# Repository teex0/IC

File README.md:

# IC 
Iniciação Científica da placa integrada do projeto RoboFEI-HT

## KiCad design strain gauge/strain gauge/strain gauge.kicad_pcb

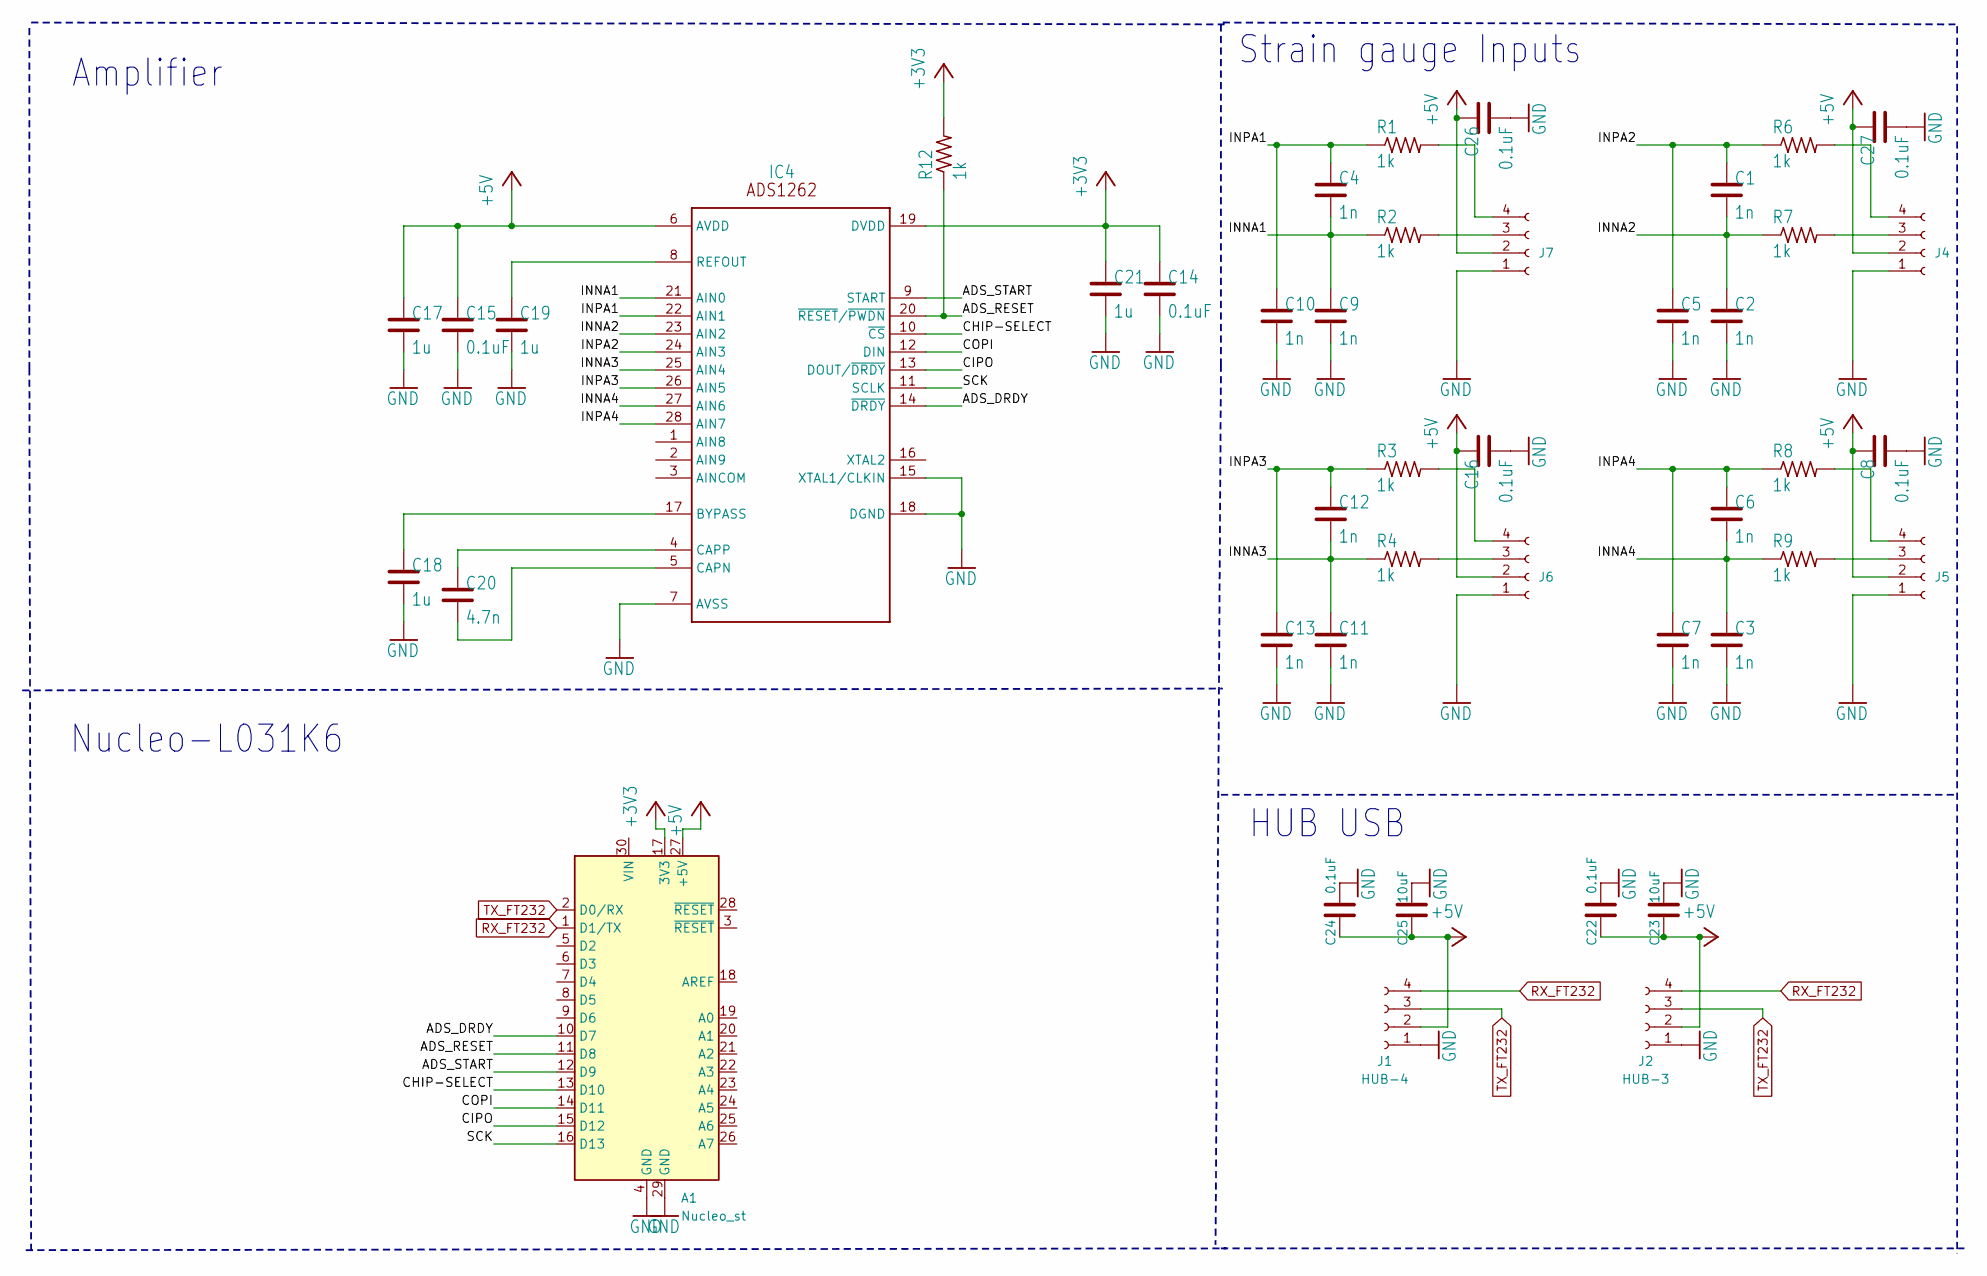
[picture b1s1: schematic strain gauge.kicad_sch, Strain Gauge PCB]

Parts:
A1: Nucleo_st; Arduino_Nano
C1, C2, C3, C4, C5, C6, C7, C9, C10, C11, C12, C13: 1n; C_1206_3216Metric_Pad1.33x1.80mm_HandSolder
C8, C14, C15, C16, C26, C27: 0.1uF; C_1206_3216Metric_Pad1.33x1.80mm_HandSolder
C17, C18, C19, C21: 1u; C_0201_0603Metric_Pad0.64x0.40mm_HandSolder
C20: 4.7n; C_1206_3216Metric_Pad1.33x1.80mm_HandSolder
C22, C24: 0.1uF; C_1206_3216Metric
C23, C25: 10uF; C_1206_3216Metric
IC4: ADS1262; ADS1262IPW
J1: HUB-4; PinHeader_1x04_P2.00mm_Vertical
J2: HUB-3; PinHeader_1x04_P2.00mm_Vertical
J4, J5, J6, J7: Conn_01x04_Socket; JST_PH_S4B-PH-K_1x04_P2.00mm_Horizontal
R1, R2, R3, R4, R6, R7, R8, R9, R12: 1k; R_1206_3216Metric_Pad1.30x1.75mm_HandSolder

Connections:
+3V3: A1.17 (3V3), C14.1, C21.1, IC4.19 (DVDD), R12.2
+5V: A1.27 (+5V), C8.1, C15.1, C16.1, C17.1, C22.1, C23.1, C24.1, C25.1, C26.1, C27.1, IC4.6 (AVDD), J1.2, J2.2, J4.2, J5.2, J6.2, J7.2
/ADS_DRDY: A1.10 (D7), IC4.14 (~DRDY)
/ADS_RESET: A1.11 (D8), IC4.20 (~RESET/~PWDN), R12.1
/ADS_START: A1.12 (D9), IC4.9 (START)
/CHIP-SELECT: A1.13 (D10), IC4.10 (~CS)
/CIPO: A1.15 (D12), IC4.13 (DOUT/~DRDY)
/COPI: A1.14 (D11), IC4.12 (DIN)
/INNA1: C4.2, C9.1, IC4.21 (AIN0), R2.1
/INNA2: C1.2, C2.1, IC4.23 (AIN2), R7.1
/INNA3: C11.1, C12.2, IC4.25 (AIN4), R4.1
/INNA4: C3.1, C6.2, IC4.27 (AIN6), R9.1
/INPA1: C4.1, C10.1, IC4.22 (AIN1), R1.1
/INPA2: C1.1, C5.1, IC4.24 (AIN3), R6.1
/INPA3: C12.1, C13.1, IC4.26 (AIN5), R3.1
/INPA4: C6.1, C7.1, IC4.28 (AIN7), R8.1
/SCK: A1.16 (D13), IC4.11 (SCLK)
GND: A1.4 (GND), A1.29 (GND), C2.2, C3.2, C5.2, C7.2, C8.2, C9.2, C10.2, C11.2, C13.2, C14.2, C15.2, C16.2, C17.2, C18.2, C19.2, C21.2, C22.2, C23.2, C24.2, C25.2, C26.2, C27.2, IC4.7 (AVSS), IC4.15 (XTAL1/CLKIN), IC4.18 (DGND), J1.1, J2.1, J4.1, J5.1, J6.1, J7.1
unnamed: C18.1, IC4.17 (BYPASS)
unnamed: C20.2, IC4.5 (CAPN)
unnamed: C20.1, IC4.4 (CAPP)
unnamed: C19.1, IC4.8 (REFOUT)
unnamed: J4.3, R7.2
unnamed: J4.4, R6.2
unnamed: J5.3, R9.2
unnamed: J5.4, R8.2
unnamed: J6.3, R4.2
unnamed: J6.4, R3.2
unnamed: J7.3, R2.2
unnamed: J7.4, R1.2
RX_FT232: A1.1 (D1/TX), J1.4, J2.4
TX_FT232: A1.2 (D0/RX), J1.3, J2.3

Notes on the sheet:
Strain gauge Inputs
Amplifier
Nucleo-L031K6
HUB USB

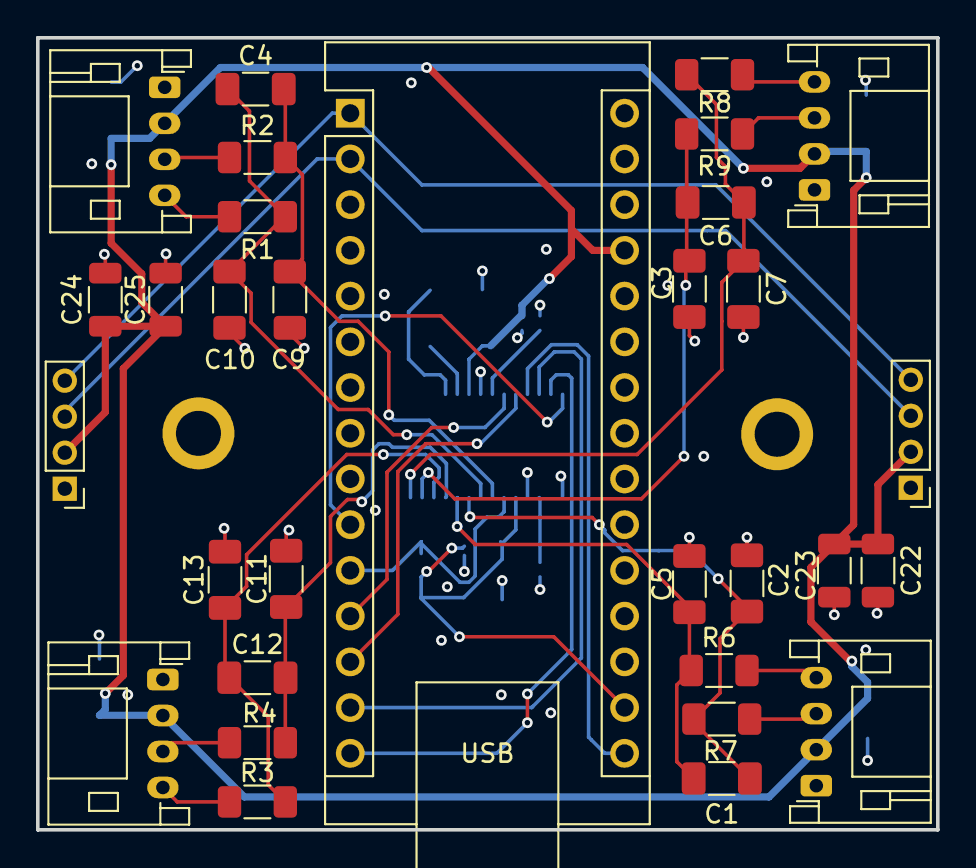
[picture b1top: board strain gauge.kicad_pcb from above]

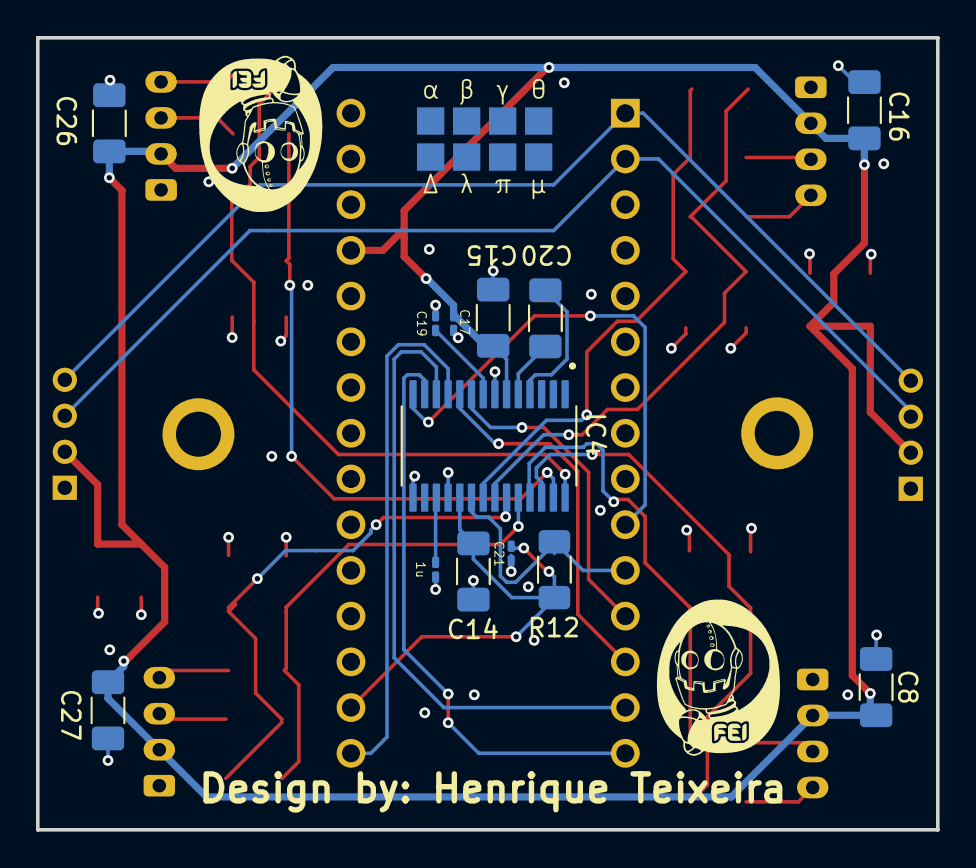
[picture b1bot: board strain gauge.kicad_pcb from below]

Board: 4 copper layers, 50.0 x 44.0 mm, 44 parts (13 on the bottom side), 32 nets.

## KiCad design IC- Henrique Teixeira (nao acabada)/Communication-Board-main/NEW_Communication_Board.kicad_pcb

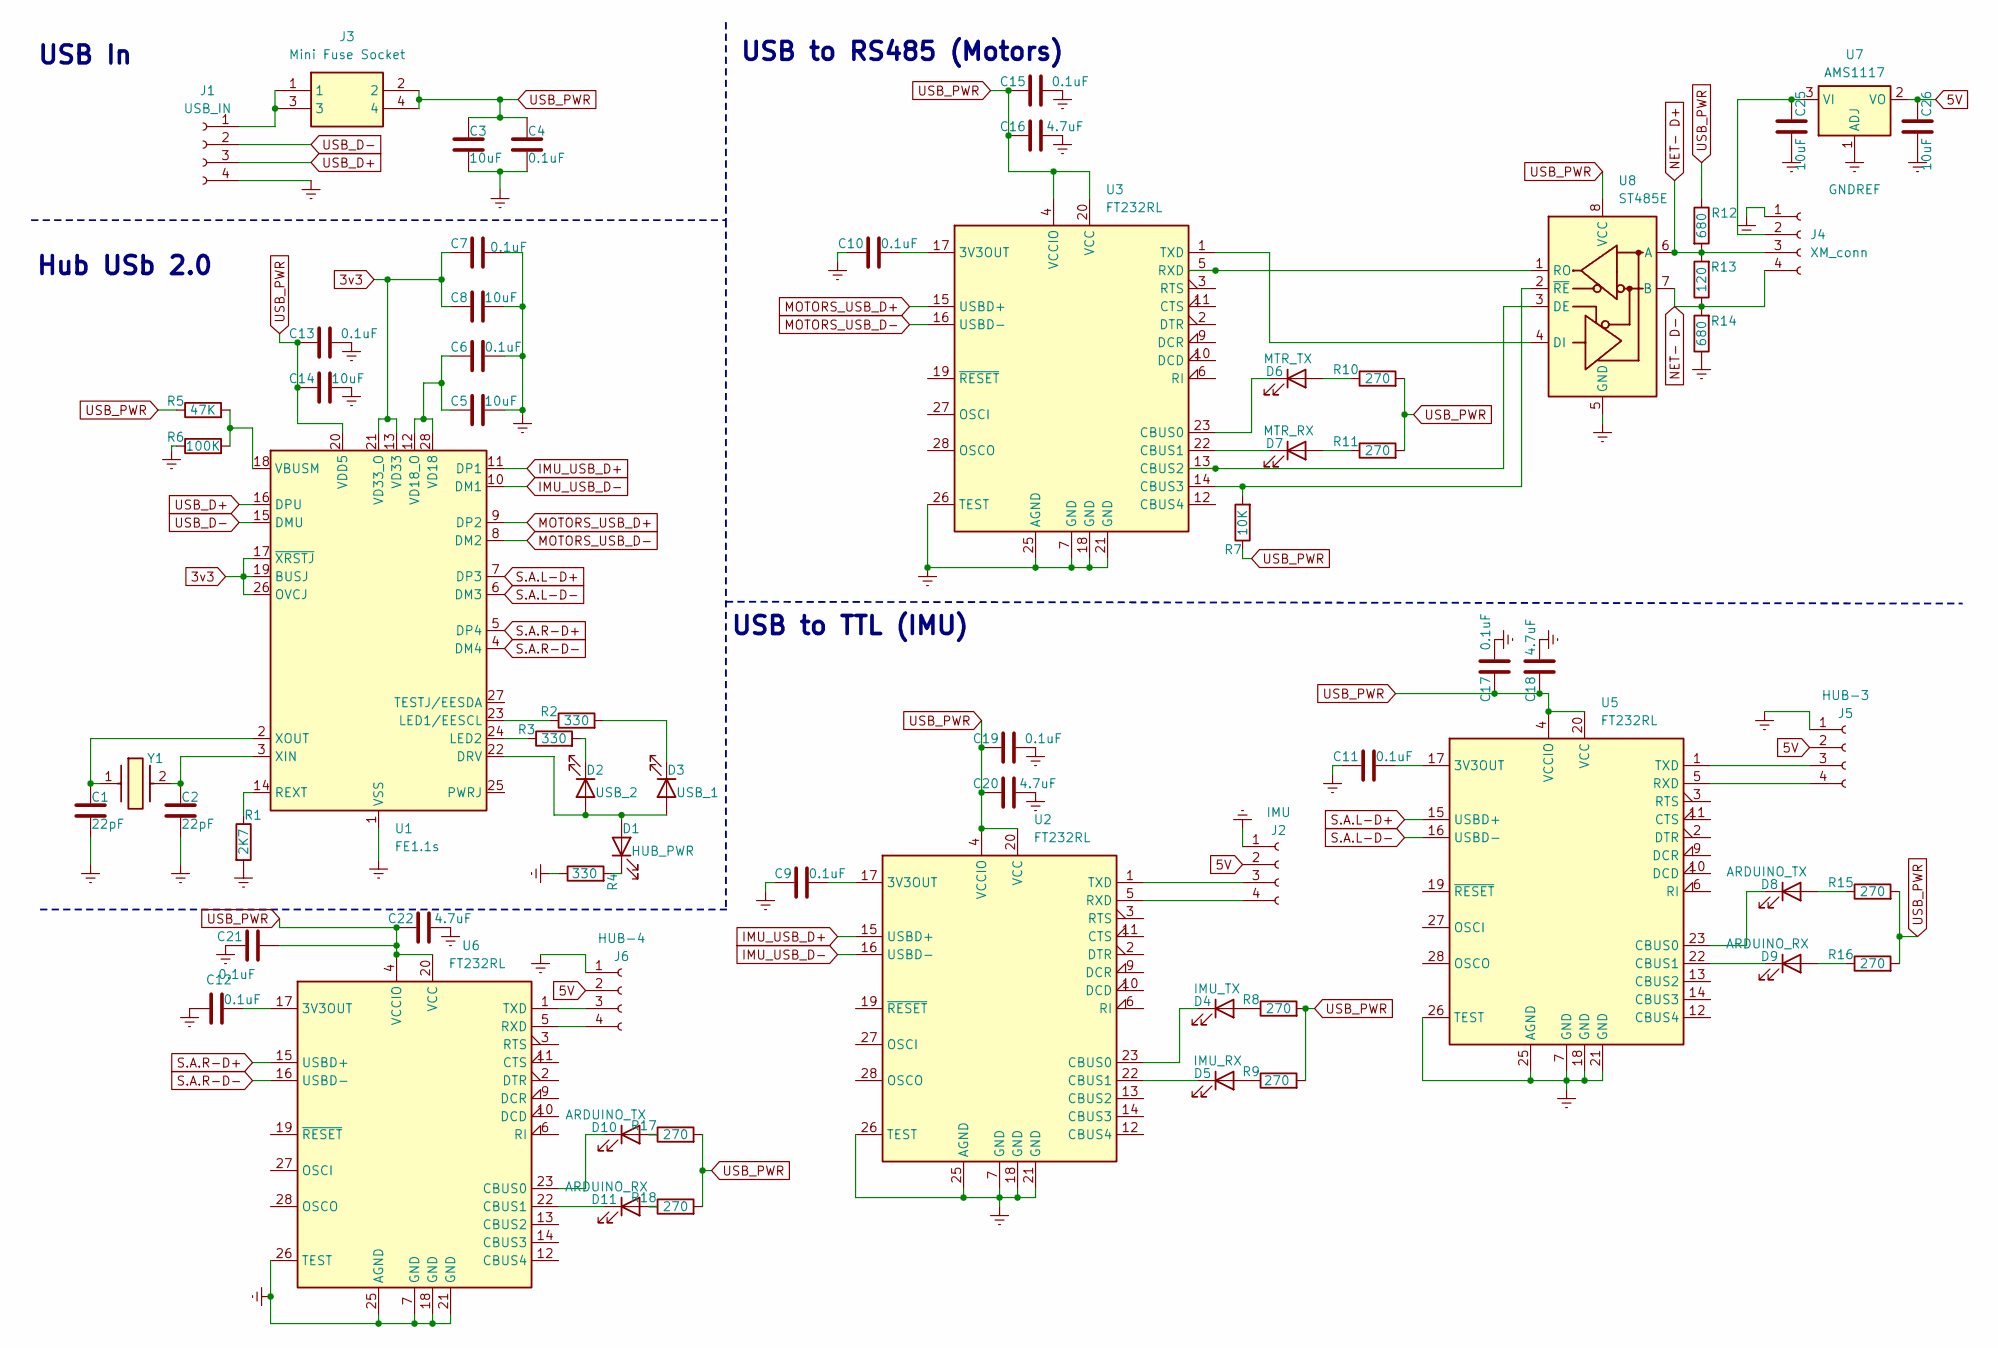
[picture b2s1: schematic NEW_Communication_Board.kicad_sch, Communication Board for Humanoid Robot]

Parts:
C1, C2: 22pF; C_1206_3216Metric
C3, C5, C8, C14, C25, C26: 10uF; C_1206_3216Metric
C4, C6, C7, C9, C10, C11, C12, C13, C15, C17, C19, C21: 0.1uF; C_1206_3216Metric
C16, C18, C20, C22: 4.7uF; C_1206_3216Metric
D1: HUB_PWR; LED_1206_3216Metric_Pad1.42x1.75mm_HandSolder
D2: USB_2; LED_1206_3216Metric_Pad1.42x1.75mm_HandSolder
D3: USB_1; LED_1206_3216Metric_Pad1.42x1.75mm_HandSolder
D4: IMU_TX; LED_1206_3216Metric_Pad1.42x1.75mm_HandSolder
D5: IMU_RX; LED_1206_3216Metric_Pad1.42x1.75mm_HandSolder
D6: MTR_TX; LED_1206_3216Metric_Pad1.42x1.75mm_HandSolder
D7: MTR_RX; LED_1206_3216Metric_Pad1.42x1.75mm_HandSolder
D8, D10: ARDUINO_TX; LED_1206_3216Metric_Pad1.42x1.75mm_HandSolder
D9, D11: ARDUINO_RX; LED_1206_3216Metric_Pad1.42x1.75mm_HandSolder
J1: USB_IN; PinHeader_1x04_P2.54mm_Vertical
J2: IMU; PinHeader_1x04_P2.54mm_Vertical
J3: Mini Fuse Socket; Mouser Part Number 534-3557-2
J4: XM_conn; XM_conn_vertical-B4B-EH-A
J5: HUB-3; PinHeader_1x04_P2.00mm_Vertical
J6: HUB-4; PinHeader_1x04_P2.00mm_Vertical
R1: 2K7; R_1206_3216Metric
R2, R3, R4: 330; R_1206_3216Metric
R5: 47K; R_1206_3216Metric
R6: 100K; R_1206_3216Metric
R7: 10K; R_1206_3216Metric
R8, R9, R10, R11, R15, R16, R17, R18: 270; R_1206_3216Metric
R12, R14: 680; R_1206_3216Metric
R13: 120; R_1206_3216Metric
U1: FE1.1s; SSOP-28_3.9x9.9mm_P0.635mm
U2, U3, U5, U6: FT232RL; SSOP-28_5.3x10.2mm_P0.65mm
U7: AMS1117; SOT-223
U8: ST485E; SOIC-8_3.9x4.9mm_P1.27mm
Y1: Crystal 12MHz - ECS; Mouser Part Number 520-120-18-5PX-GM-TR

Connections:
3v3: C7.1, C8.1, U1.13 (VD33), U1.17 (~XRSTJ), U1.19 (BUSJ), U1.21 (VD33_O), U1.26 (OVCJ)
5V: C26.1, J2.2, J5.2, J6.2, U7.2 (VO)
GNDREF: C1.2, C2.2, C3.2, C4.2, C5.2, C6.2, C7.2, C8.2, C9.1, C10.1, C11.1, C12.1, C13.2, C14.2, C15.2, C16.2, C17.2, C18.2, C19.2, C20.2, C21.1, C22.2, C25.2, C26.2, J1.4, J2.1, J4.1 (GND), J5.1, J6.1, R1.2, R4.1, R6.1, R14.1, U1.1 (VSS), U2.7 (GND), U2.18 (GND), U2.21 (GND), U2.25 (AGND), U2.26 (TEST), U3.7 (GND), U3.18 (GND), U3.21 (GND), U3.25 (AGND), U3.26 (TEST), U5.7 (GND), U5.18 (GND), U5.21 (GND), U5.25 (AGND), U5.26 (TEST), U6.7 (GND), U6.18 (GND), U6.21 (GND), U6.25 (AGND), U6.26 (TEST), U7.1 (ADJ), U8.5 (GND)
IMU_USB_D+: U1.11 (DP1), U2.15 (USBD+)
IMU_USB_D-: U1.10 (DM1), U2.16 (USBD-)
MOTORS_USB_D+: U1.9 (DP2), U3.15 (USBD+)
MOTORS_USB_D-: U1.8 (DM2), U3.16 (USBD-)
NET- D+: J4.3 (D+), R12.2, R13.2, U8.6 (A)
NET- D-: J4.4 (D-), R13.1, R14.2, U8.7 (B)
unnamed: D1.2 (A), D2.2 (A), D3.2 (A), U1.22 (DRV)
unnamed: D1.1 (K), R4.2
unnamed: D2.1 (K), R3.2
unnamed: D3.1 (K), R2.2
unnamed: D4.2 (A), R8.1
unnamed: D4.1 (K), U2.23 (CBUS0)
unnamed: D5.2 (A), R9.1
unnamed: D5.1 (K), U2.22 (CBUS1)
unnamed: D6.2 (A), R10.1
unnamed: D6.1 (K), U3.23 (CBUS0)
unnamed: D7.2 (A), R11.1
unnamed: D7.1 (K), U3.22 (CBUS1)
unnamed: D8.2 (A), R15.1
unnamed: D8.1 (K), U5.23 (CBUS0)
unnamed: D9.2 (A), R16.1
unnamed: D9.1 (K), U5.22 (CBUS1)
unnamed: D10.2 (A), R17.1
unnamed: D10.1 (K), U6.23 (CBUS0)
unnamed: D11.2 (A), R18.1
unnamed: D11.1 (K), U6.22 (CBUS1)
unnamed: J1.1, J3.1, J3.3
unnamed: J2.3, U2.1 (TXD)
unnamed: J2.4, U2.5 (RXD)
unnamed: C25.1, J4.2 (VDD), U7.3 (VI)
unnamed: J5.3, U5.1 (TXD)
unnamed: J5.4, U5.5 (RXD)
unnamed: J6.3, U6.1 (TXD)
unnamed: J6.4, U6.5 (RXD)
unnamed: R2.1, U1.23 (LED1/EESCL)
unnamed: R3.1, U1.24 (LED2)
unnamed: R1.1, U1.14 (REXT)
unnamed: R5.2, R6.2, U1.18 (VBUSM)
unnamed: C5.1, C6.1, U1.12 (VD18_O), U1.28 (VD18)
unnamed: C2.1, U1.3 (XIN), Y1.2
unnamed: C1.1, U1.2 (XOUT), Y1.1
unnamed: C9.2, U2.17 (3V3OUT)
unnamed: C10.2, U3.17 (3V3OUT)
unnamed: U3.13 (CBUS2), U8.3 (DE)
unnamed: R7.2, U3.14 (CBUS3), U8.2 (~RE)
unnamed: U3.5 (RXD), U8.1 (RO)
unnamed: U3.1 (TXD), U8.4 (DI)
unnamed: C11.2, U5.17 (3V3OUT)
unnamed: C12.2, U6.17 (3V3OUT)
S.A.L-D+: U1.7 (DP3), U5.15 (USBD+)
S.A.L-D-: U1.6 (DM3), U5.16 (USBD-)
S.A.R-D+: U1.5 (DP4), U6.15 (USBD+)
S.A.R-D-: U1.4 (DM4), U6.16 (USBD-)
USB_D+: J1.3, U1.16 (DPU)
USB_D-: J1.2, U1.15 (DMU)
USB_PWR: C3.1, C4.1, C13.1, C14.1, C15.1, C16.1, C17.1, C18.1, C19.1, C20.1, C21.2, C22.1, J3.2, J3.4, R5.1, R7.1, R8.2, R9.2, R10.2, R11.2, R12.1, R15.2, R16.2, R17.2, R18.2, U1.20 (VDD5), U2.4 (VCCIO), U2.20 (VCC), U3.4 (VCCIO), U3.20 (VCC), U5.4 (VCCIO), U5.20 (VCC), U6.4 (VCCIO), U6.20 (VCC), U8.8 (VCC)

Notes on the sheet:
USB In
USB to RS485 (Motors)
Hub USb 2.0
USB to TTL (IMU)

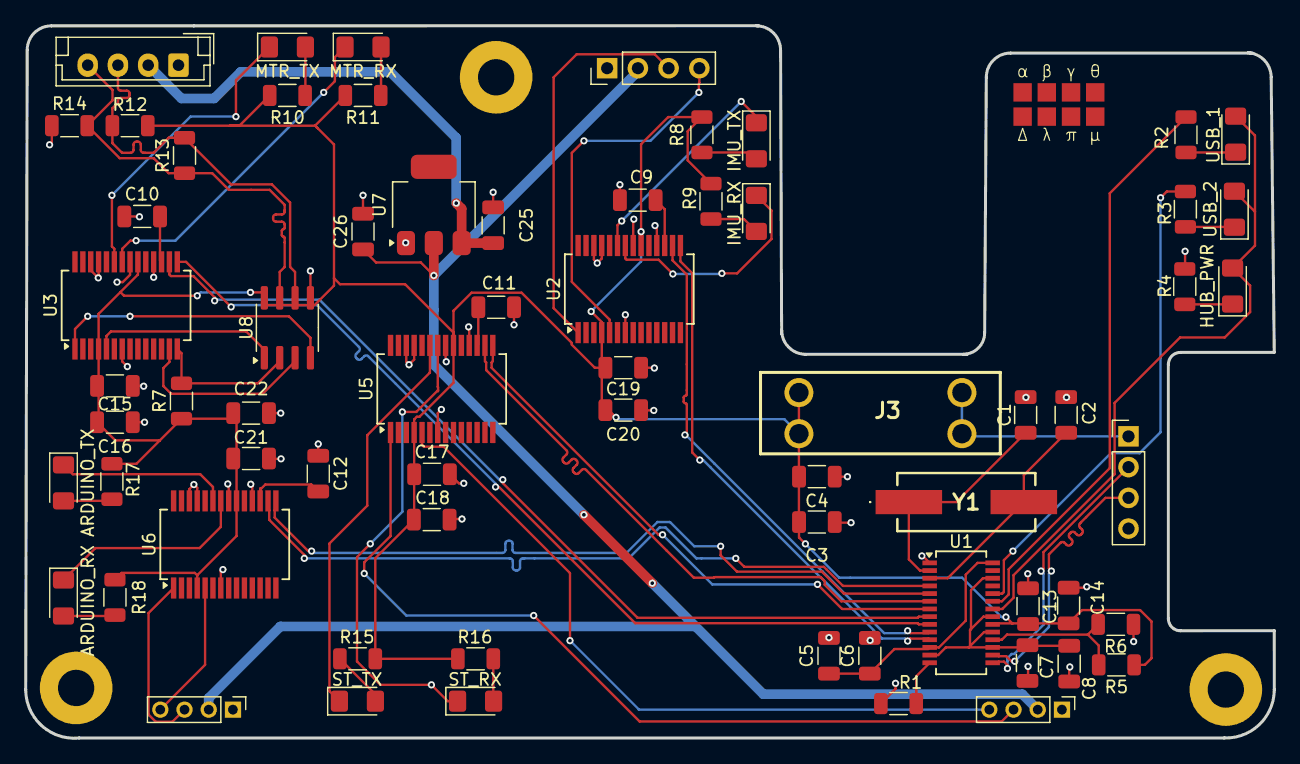
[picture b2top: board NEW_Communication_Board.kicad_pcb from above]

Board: 4 copper layers, 103.2 x 58.9 mm, 67 parts (0 on the bottom side), 59 nets.

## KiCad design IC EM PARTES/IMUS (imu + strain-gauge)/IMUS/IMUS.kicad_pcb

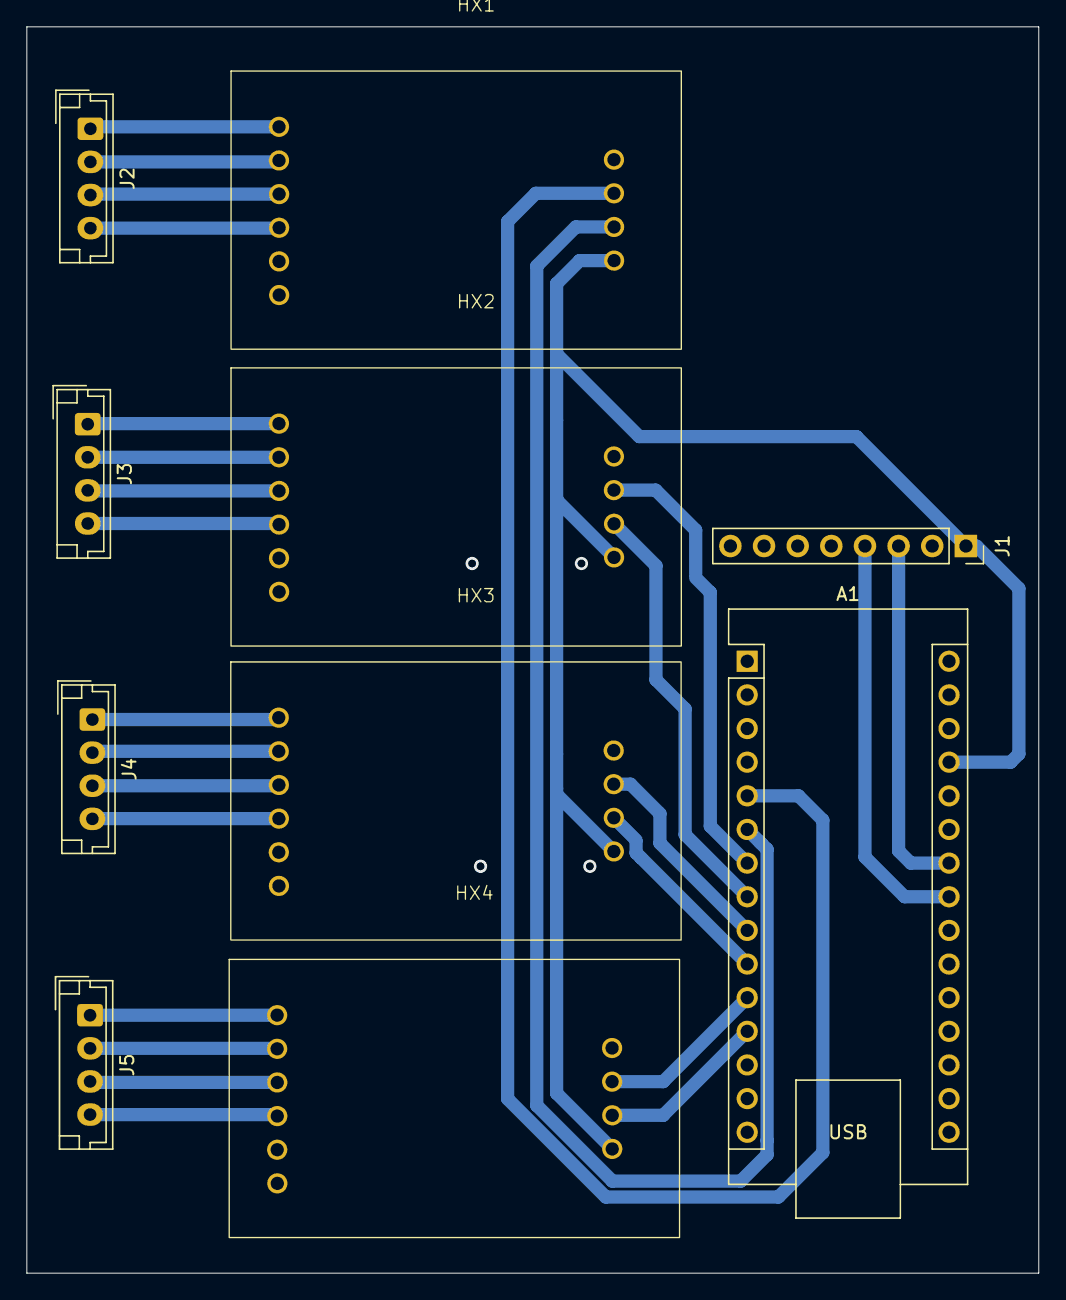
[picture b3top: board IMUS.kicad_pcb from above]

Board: 2 copper layers, 76.4 x 94.1 mm, 10 parts (0 on the bottom side), 28 nets.

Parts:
A1: Arduino_Nano_v3.x; Arduino_Nano
HX1, HX2, HX3, HX4: HX711 MODULE
J1: IMU; PinSocket_1x08_P2.54mm_Vertical
J2, J3, J4, J5: XM_conn; XM_conn_vertical-B4B-EH-A

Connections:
GND: A1.4 (GND), A1.29 (GND), HX1.1 (GND), HX2.1 (GND), HX3.1 (GND), HX4.1 (GND), J1.2
unnamed: A1.27 (+5V), HX1.4 (VCC), HX2.4 (VCC), HX3.4 (VCC), HX4.4 (VCC), J1.1
unnamed: A1.23 (A4), J1.4
unnamed: A1.24 (A5), J1.3
unnamed: A1.5 (D2), HX1.2 (DT)
unnamed: A1.6 (D3), HX1.3 (SCK)
unnamed: A1.7 (D4), HX2.2 (DT)
unnamed: A1.8 (D5), HX2.3 (SCK)
unnamed: A1.9 (D6), HX3.2 (DT)
unnamed: A1.10 (D7), HX3.3 (SCK)
unnamed: A1.11 (D8), HX4.2 (DT)
unnamed: A1.12 (D9), HX4.3 (SCK)
unnamed: HX1.8, J2.4 (D-)
unnamed: HX1.7, J2.3 (D+)
unnamed: HX1.5, J2.1 (GND)
unnamed: HX1.6, J2.2 (VDD)
unnamed: HX2.8, J3.4 (D-)
unnamed: HX2.7, J3.3 (D+)
unnamed: HX2.5, J3.1 (GND)
unnamed: HX2.6, J3.2 (VDD)
unnamed: HX3.8, J4.4 (D-)
unnamed: HX3.7, J4.3 (D+)
unnamed: HX3.5, J4.1 (GND)
unnamed: HX3.6, J4.2 (VDD)
unnamed: HX4.8, J5.4 (D-)
unnamed: HX4.7, J5.3 (D+)
unnamed: HX4.5, J5.1 (GND)
unnamed: HX4.6, J5.2 (VDD)

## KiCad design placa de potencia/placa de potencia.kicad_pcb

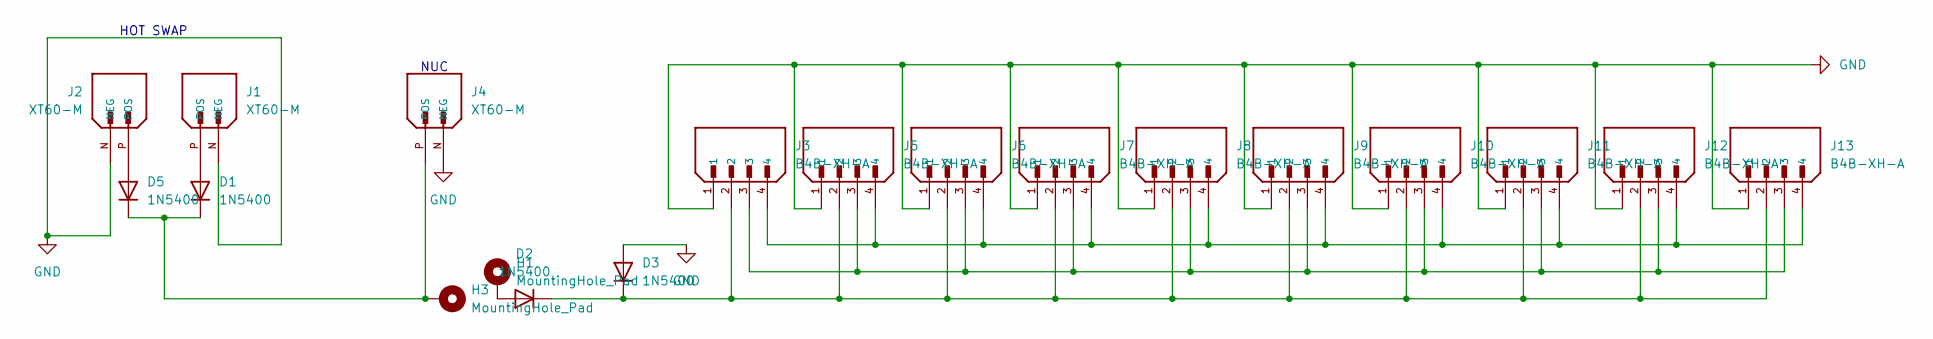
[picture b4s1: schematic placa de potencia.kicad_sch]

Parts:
D1, D2, D3, D5: 1N5400; D_DO-201AD_P15.24mm_Horizontal
H1, H3: MountingHole_Pad; MountingHole_2.5mm_Pad
J1, J2, J4: XT60-M; AMASS_XT60-M; PARTREV V1.2
J3, J5, J6, J7, J8, J9, J10, J11, J12, J13: B4B-XH-A; JST_B4B-XH-A; PARTREV 7/4/21

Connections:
GND: D3.2 (A), J1.N (NEG), J2.N (NEG), J3.1, J4.N (NEG), J5.1, J6.1, J7.1, J8.1, J9.1, J10.1, J11.1, J12.1, J13.1
unnamed: D1.2 (A), J1.P (POS)
unnamed: D1.1 (K), D5.1 (K), H3.1, J4.P (POS)
unnamed: D2.2 (A), H1.1
unnamed: D2.1 (K), D3.1 (K), J3.2, J5.2, J6.2, J7.2, J8.2, J9.2, J10.2, J11.2, J12.2, J13.2
unnamed: D5.2 (A), J2.P (POS)
unnamed: J3.3, J5.3, J6.3, J7.3, J8.3, J9.3, J10.3, J11.3, J12.3, J13.3
unnamed: J3.4, J5.4, J6.4, J7.4, J8.4, J9.4, J10.4, J11.4, J12.4, J13.4

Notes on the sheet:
NUC
HOT SWAP

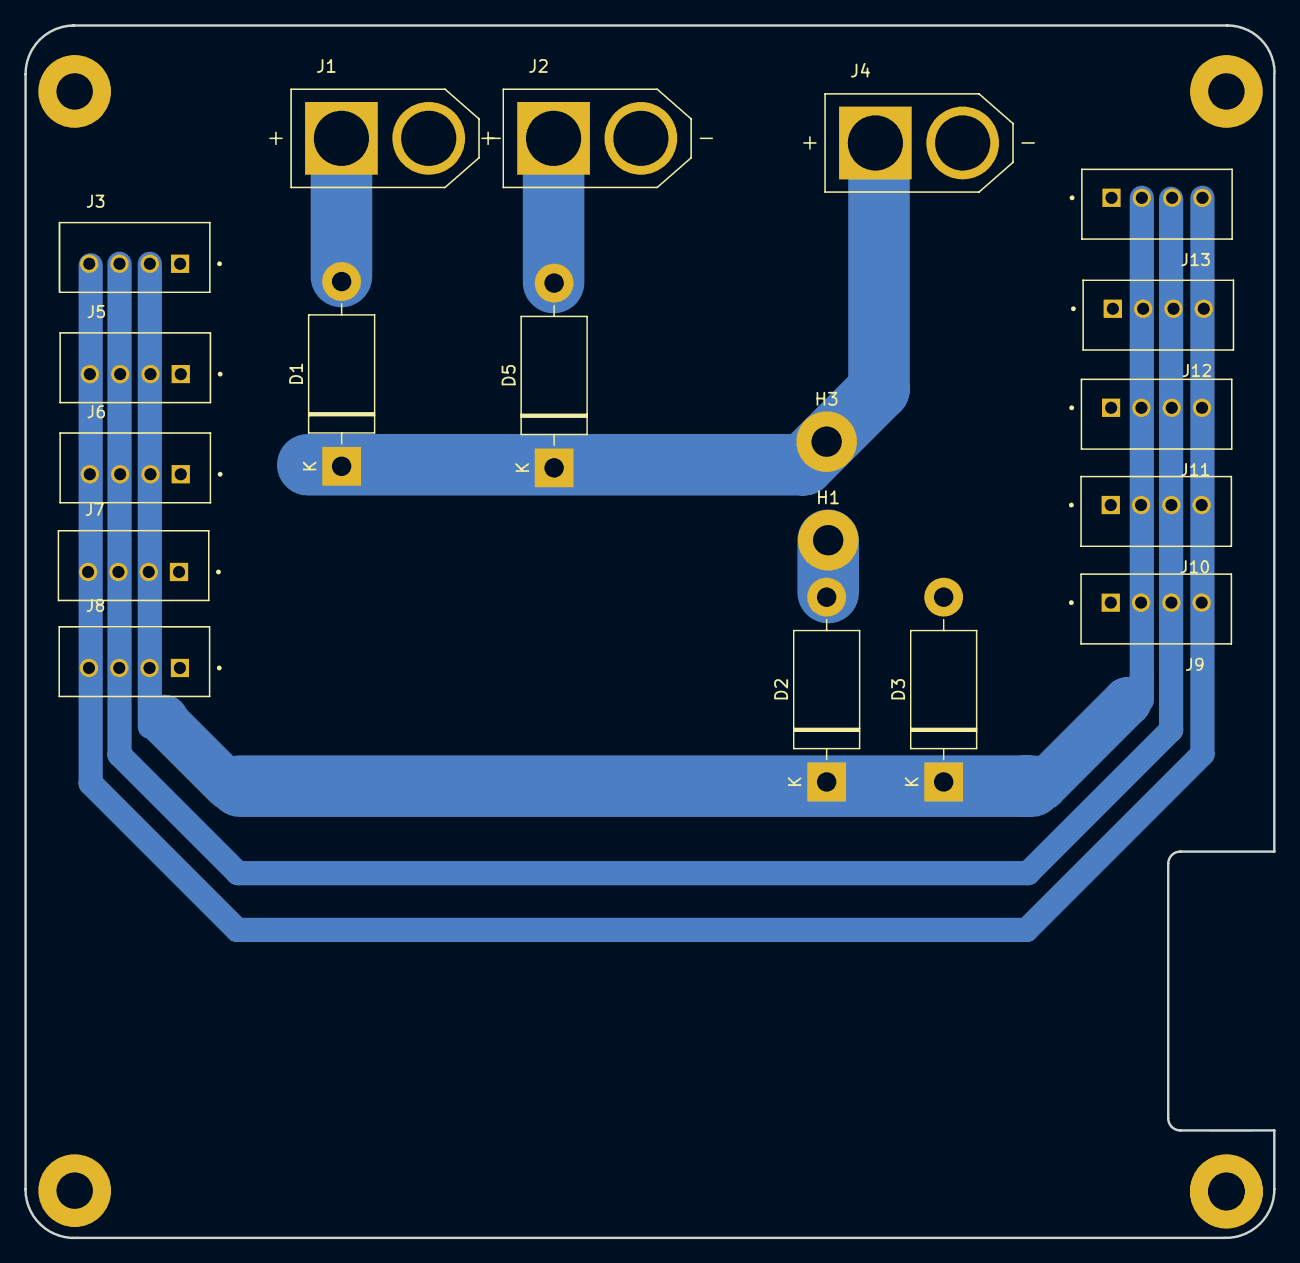
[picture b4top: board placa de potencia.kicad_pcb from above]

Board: 2 copper layers, 103.0 x 100.0 mm, 19 parts (0 on the bottom side), 8 nets.

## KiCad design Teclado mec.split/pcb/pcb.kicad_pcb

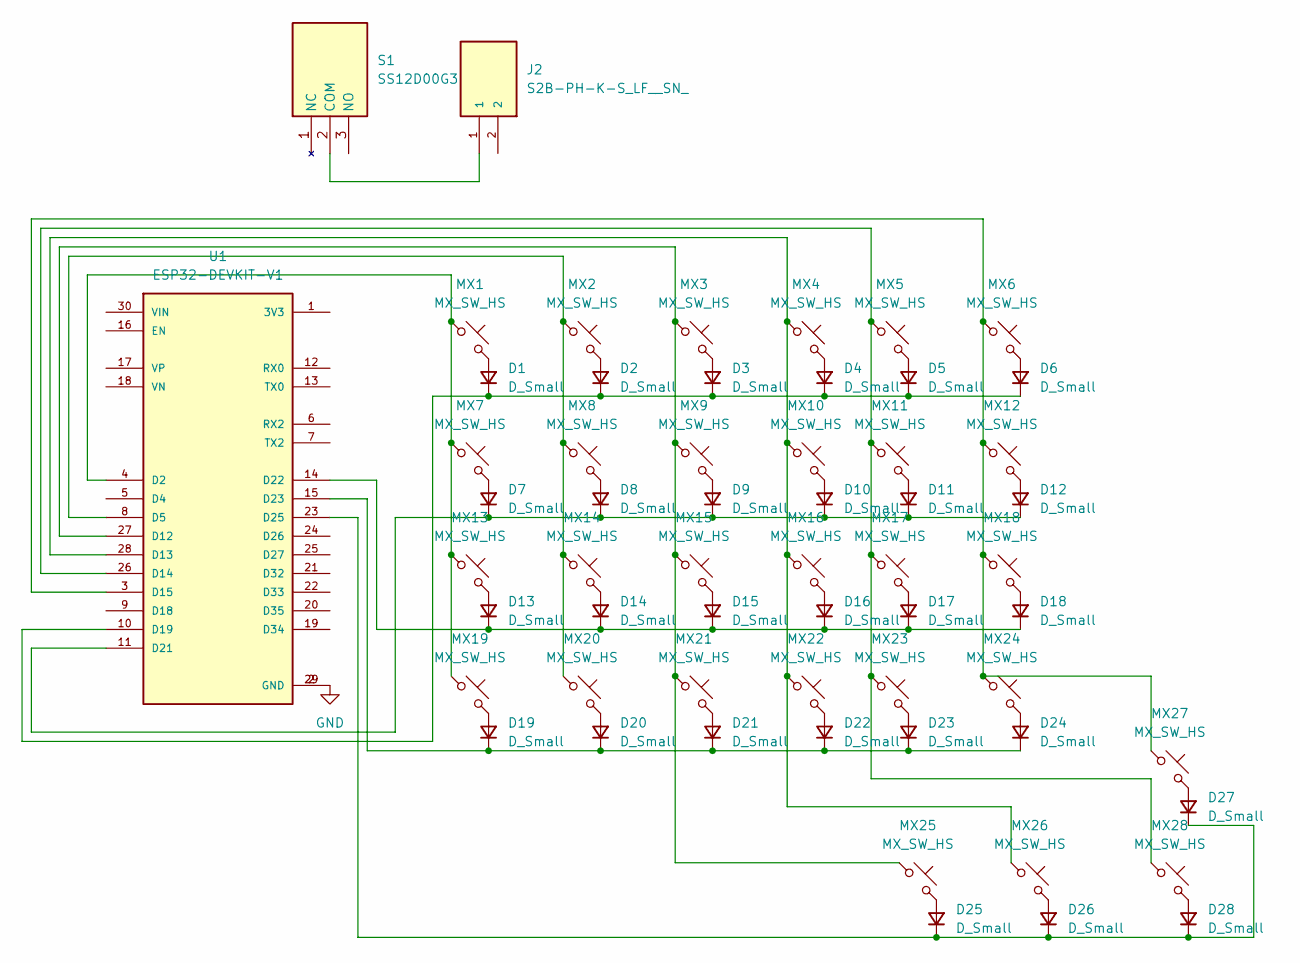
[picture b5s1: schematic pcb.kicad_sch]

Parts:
D1, D2, D3, D4, D5, D6, D7, D8, D9, D10, D11, D12, D13, D14, D15, D16, D17, D18, D19, D20, D21, D22, D23, D24, D25, D26, D27, D28: D_Small; D_SOD-123
J2: S2B-PH-K-S_LF__SN_; JST_S2B-PH-K-S_LF__SN_
MX1, MX2, MX3, MX4, MX5, MX6, MX7, MX8, MX9, MX10, MX11, MX12, MX13, MX14, MX15, MX16, MX17, MX18, MX19, MX20, MX21, MX22, MX23, MX24, MX25, MX26, MX27, MX28: MX_SW_HS; SW_MX_HS_CPG151101S11_1u
S1: SS12D00G3; Manufacturer_Part_Number SS12D00G3
U1: ESP32-DEVKIT-V1; MODULE_ESP32_DEVKIT_V1; PARTREV N/A

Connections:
GND: U1.2 (GND), U1.29 (GND); also elsewhere on the board
unnamed: D1.2 (A), MX1.2
unnamed: D1.1 (K), D2.1 (K), D3.1 (K), D4.1 (K), D5.1 (K), D6.1 (K), U1.10 (D19)
unnamed: D2.2 (A), MX2.2
unnamed: D3.2 (A), MX3.2
unnamed: D4.2 (A), MX4.2
unnamed: D5.2 (A), MX5.2
unnamed: D6.2 (A), MX6.2
unnamed: D7.2 (A), MX7.2
unnamed: D8.2 (A), MX8.2
unnamed: D9.2 (A), MX9.2
unnamed: D10.2 (A), MX10.2
unnamed: D7.1 (K), D8.1 (K), D9.1 (K), D10.1 (K), D11.1 (K), D12.1 (K), U1.11 (D21)
unnamed: D11.2 (A), MX11.2
unnamed: D12.2 (A), MX12.2
unnamed: D13.2 (A), MX13.2
unnamed: D13.1 (K), D14.1 (K), D15.1 (K), D16.1 (K), D17.1 (K), D18.1 (K), U1.14 (D22)
unnamed: D14.2 (A), MX14.2
unnamed: D15.2 (A), MX15.2
unnamed: D16.2 (A), MX16.2
unnamed: D17.2 (A), MX17.2
unnamed: D18.2 (A), MX18.2
unnamed: D19.2 (A), MX19.2
unnamed: D19.1 (K), D20.1 (K), D21.1 (K), D22.1 (K), D23.1 (K), D24.1 (K), U1.15 (D23)
unnamed: D20.2 (A), MX20.2
unnamed: D21.2 (A), MX21.2
unnamed: D22.2 (A), MX22.2
unnamed: D23.2 (A), MX23.2
unnamed: D24.2 (A), MX24.2
unnamed: D25.2 (A), MX25.2
unnamed: D25.1 (K), D26.1 (K), D27.1 (K), D28.1 (K), U1.23 (D25)
unnamed: D26.2 (A), MX26.2
unnamed: D27.2 (A), MX27.2
unnamed: D28.2 (A), MX28.2
unnamed: J2.1, S1.2 (COM)
unnamed: MX1.1, MX7.1, MX13.1, MX19.1, U1.4 (D2)
unnamed: MX2.1, MX8.1, MX14.1, MX20.1, U1.8 (D5)
unnamed: MX3.1, MX9.1, MX15.1, MX21.1, MX25.1, U1.27 (D12)
unnamed: MX5.1, MX11.1, MX17.1, MX23.1, MX28.1, U1.26 (D14)

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
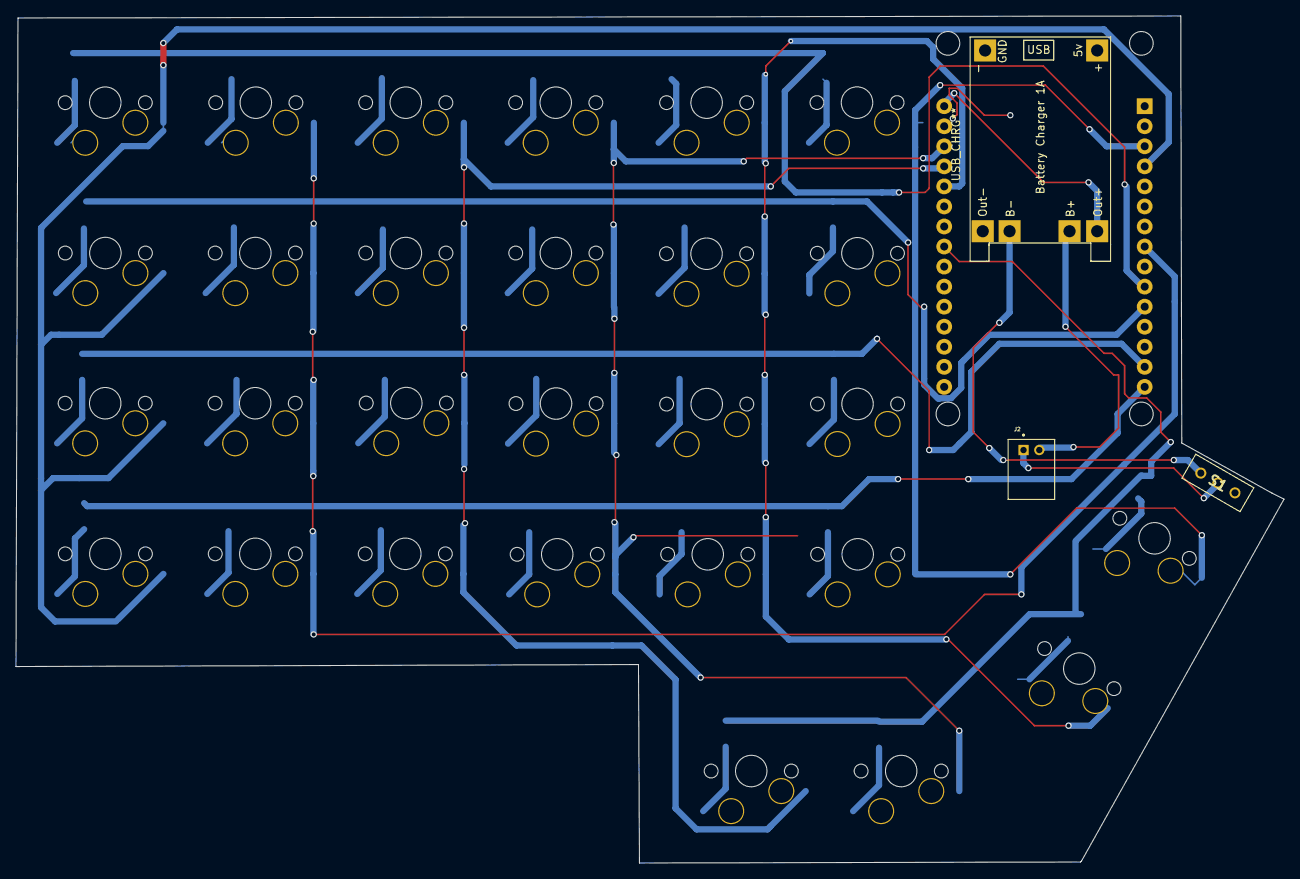
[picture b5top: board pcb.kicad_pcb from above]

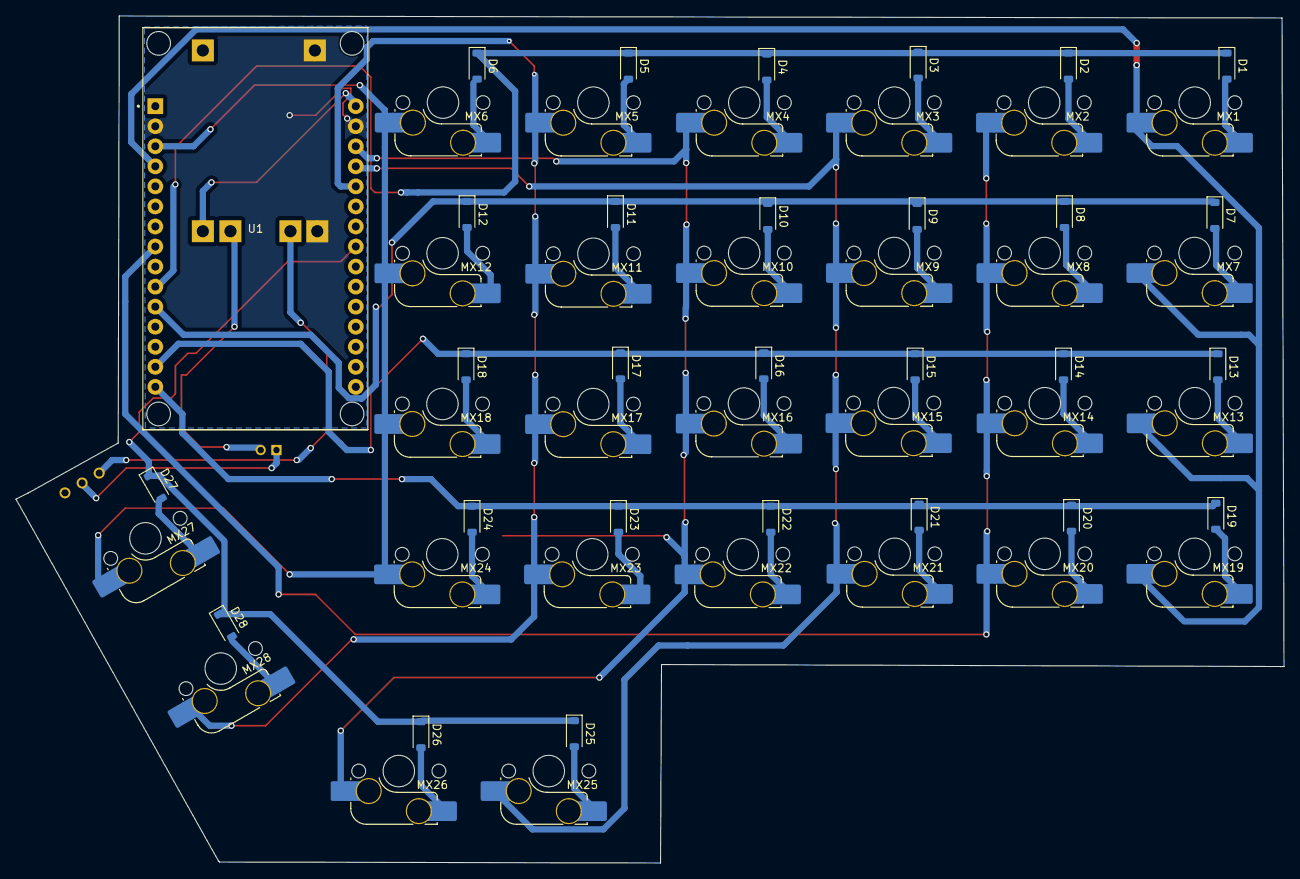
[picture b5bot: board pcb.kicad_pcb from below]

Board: 2 copper layers, 160.7 x 107.3 mm, 60 parts (57 on the bottom side), 40 nets.

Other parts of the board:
USB_CHRG**: TP4056-18650

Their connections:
GND: USB_CHRG**.2, USB_CHRG**.4; also elsewhere on the board

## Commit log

2024-08-26 teste
2024-08-26 placa da imu com arduino para teste
2024-08-27 primeiro protótipo da placa integrada (comunicação e potencia)
2024-08-29 imu nova (MPU6050)
2024-08-30 mudei o tamanho da trilha para impressão
2024-10-05 Adionei o arduino na placa integrada (nao terminei) Adicionei a pasta de teclado (projeto pessoal)
2024-10-07 Projeto do teclado mecanico split
2025-10-31 mudanças
2025-10-31 V2 communication Board
2025-10-31 ADS1262 power fixed
